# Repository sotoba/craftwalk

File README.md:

# craftWalk

macro pad for (mine)?(crafter|creator).

## Documents

- [build guide](docs/build_guid.md)
- [default keymap](docs/keymap.md)

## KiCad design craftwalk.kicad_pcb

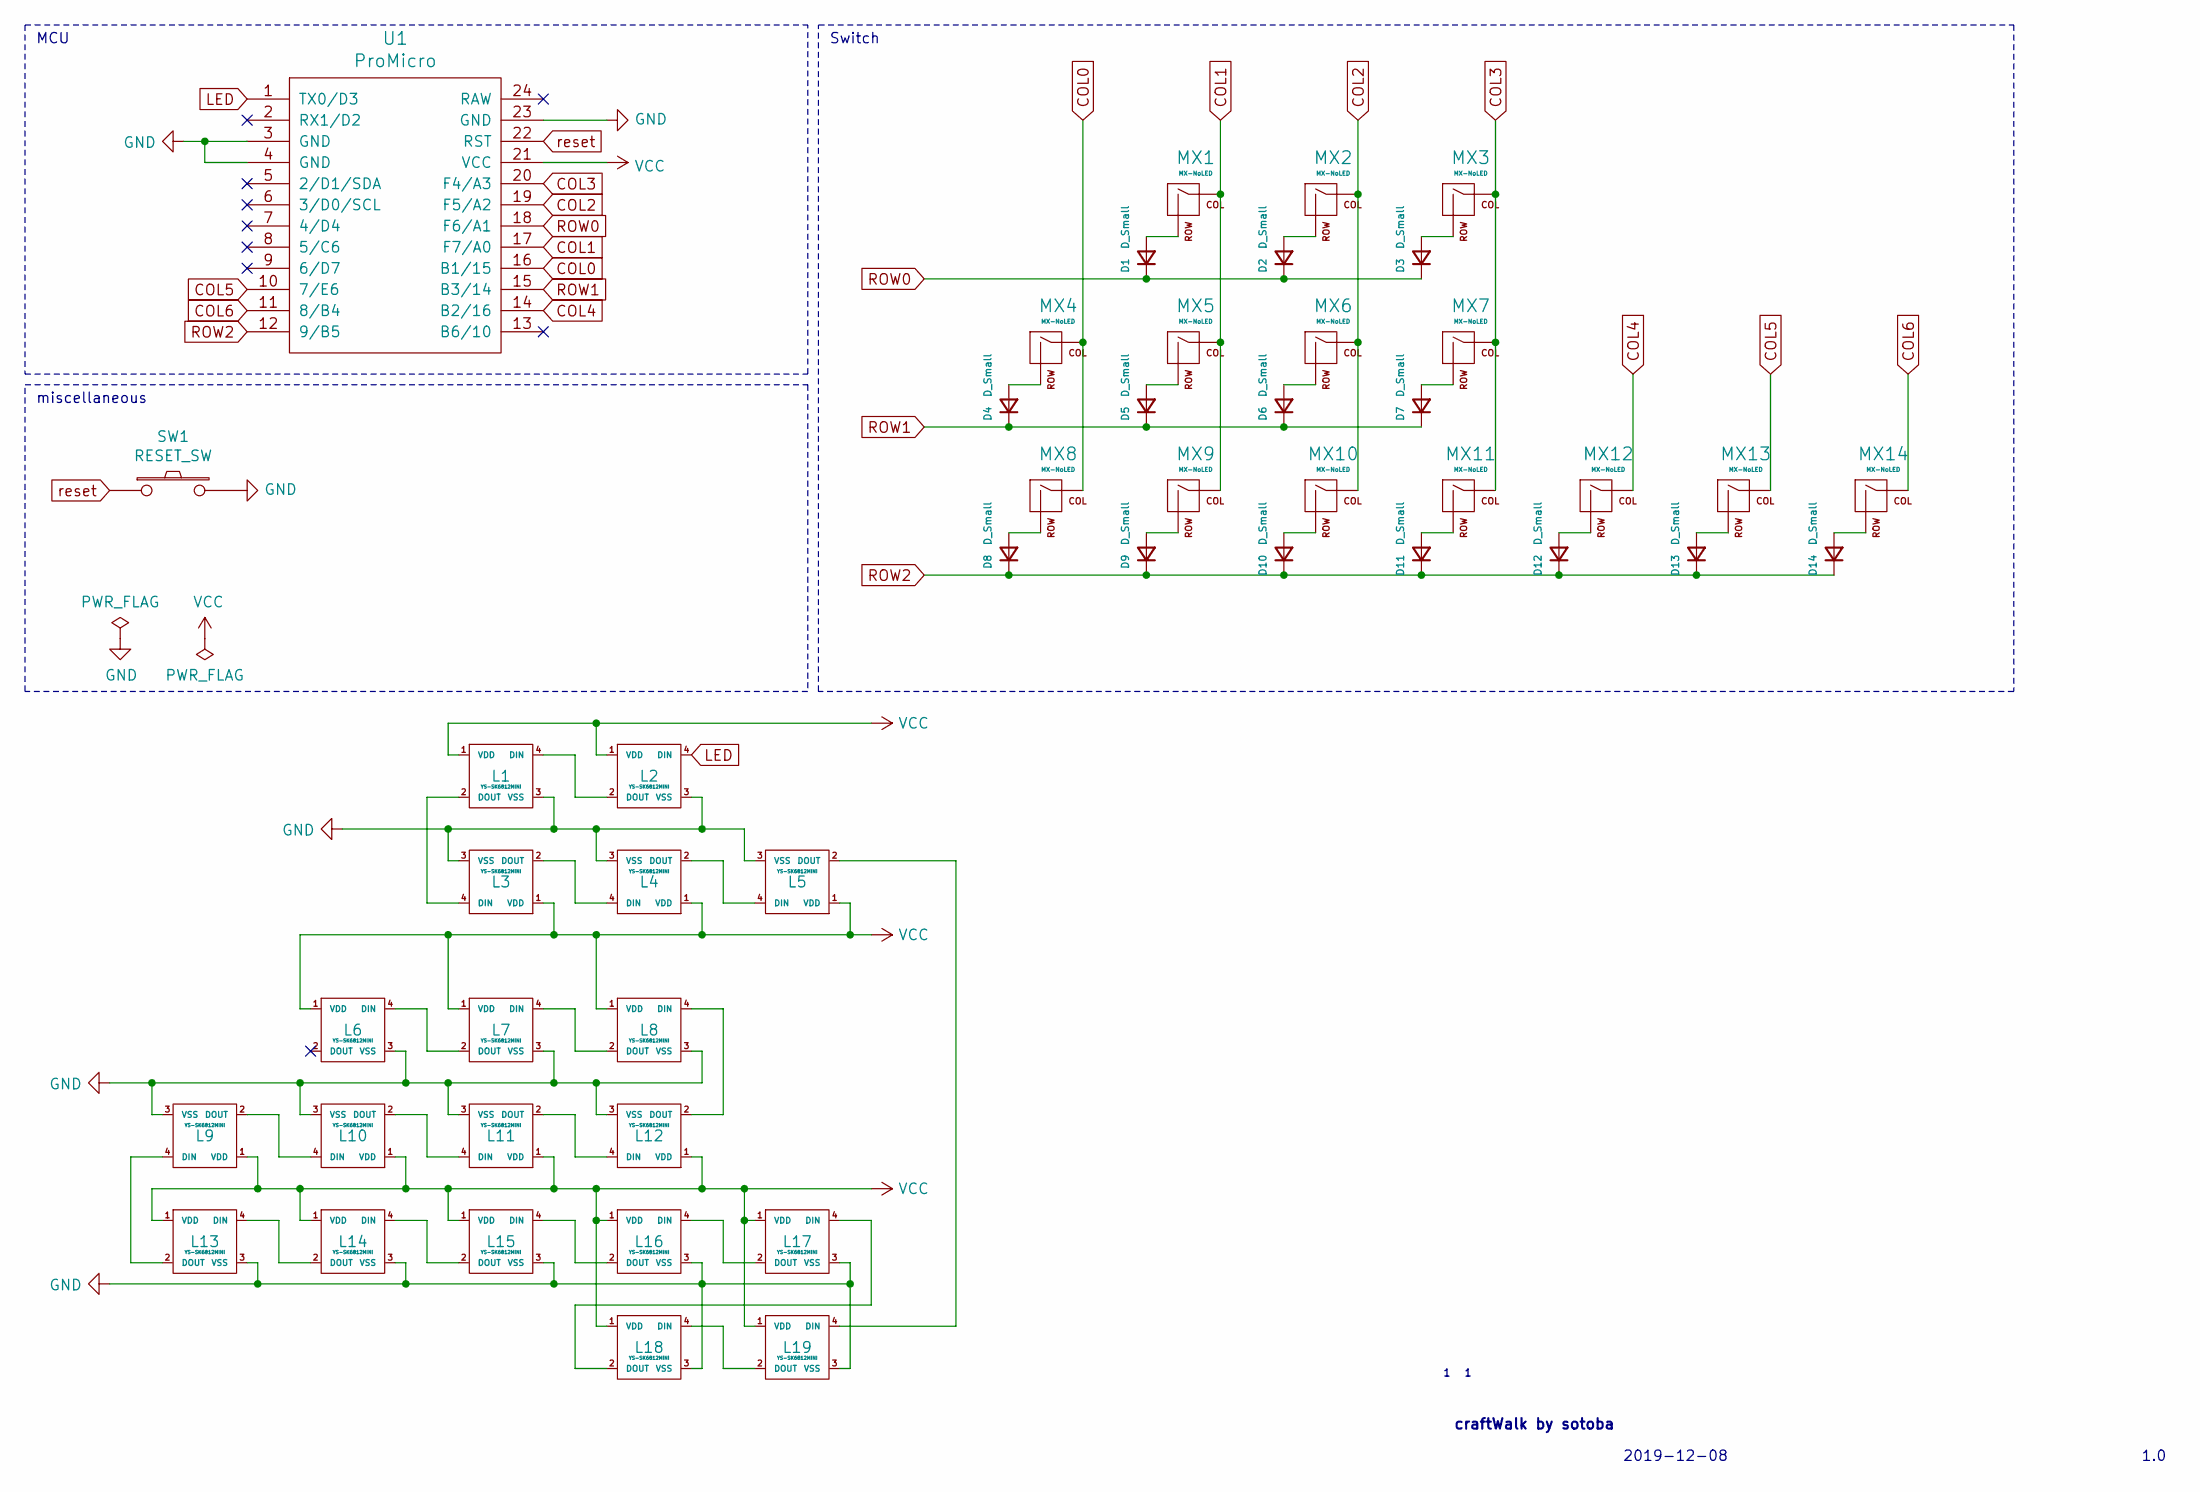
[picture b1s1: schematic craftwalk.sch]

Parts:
D1, D2, D3, D4, D5, D6, D7, D8, D9, D10, D11, D12, D13, D14: D_Small; D3_SMD
L1, L2, L3, L4, L5: YS-SK6812MINI; YS-SK6812
L6, L7, L8, L9, L10, L11, L12, L13, L14, L15, L16, L17, L18, L19: YS-SK6812MINI; YS-SK6812-underglow
MX1, MX2, MX3, MX4, MX5, MX6, MX7, MX8, MX9, MX10, MX11, MX12: MX-NoLED; MXOnly-1U-Hotswap
MX13, MX14: MX-NoLED; MXOnly-1.5U-Hotswap
SW1: RESET_SW; SKQGADE010
U1: ProMicro; ProMicro_v2

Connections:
COL0: MX4.1 (COL), MX8.1 (COL), U1.16 (B1/15)
COL1: MX1.1 (COL), MX5.1 (COL), MX9.1 (COL), U1.17 (F7/A0)
COL2: MX2.1 (COL), MX6.1 (COL), MX10.1 (COL), U1.19 (F5/A2)
COL3: MX3.1 (COL), MX7.1 (COL), MX11.1 (COL), U1.20 (F4/A3)
COL4: MX12.1 (COL), U1.14 (B2/16)
COL5: MX13.1 (COL), U1.10 (7/E6)
COL6: MX14.1 (COL), U1.11 (8/B4)
GND: L1.3 (VSS), L2.3 (VSS), L3.3 (VSS), L4.3 (VSS), L5.3 (VSS), L6.3 (VSS), L7.3 (VSS), L8.3 (VSS), L9.3 (VSS), L10.3 (VSS), L11.3 (VSS), L12.3 (VSS), L13.3 (VSS), L14.3 (VSS), L15.3 (VSS), L16.3 (VSS), L17.3 (VSS), L18.3 (VSS), L19.3 (VSS), SW1.2, U1.3 (GND), U1.4 (GND), U1.23 (GND)
LED: L2.4 (DIN), U1.1 (TX0/D3)
unnamed: D1.2 (A), MX1.2 (ROW)
unnamed: D2.2 (A), MX2.2 (ROW)
unnamed: D3.2 (A), MX3.2 (ROW)
unnamed: D4.2 (A), MX4.2 (ROW)
unnamed: D5.2 (A), MX5.2 (ROW)
unnamed: D6.2 (A), MX6.2 (ROW)
unnamed: D7.2 (A), MX7.2 (ROW)
unnamed: D8.2 (A), MX8.2 (ROW)
unnamed: D9.2 (A), MX9.2 (ROW)
unnamed: D10.2 (A), MX10.2 (ROW)
unnamed: D11.2 (A), MX11.2 (ROW)
unnamed: D12.2 (A), MX12.2 (ROW)
unnamed: D13.2 (A), MX13.2 (ROW)
unnamed: D14.2 (A), MX14.2 (ROW)
unnamed: L1.2 (DOUT), L3.4 (DIN)
unnamed: L1.4 (DIN), L2.2 (DOUT)
unnamed: L3.2 (DOUT), L4.4 (DIN)
unnamed: L4.2 (DOUT), L5.4 (DIN)
unnamed: L6.4 (DIN), L7.2 (DOUT)
unnamed: L7.4 (DIN), L8.2 (DOUT)
unnamed: L10.2 (DOUT), L11.4 (DIN)
unnamed: L9.2 (DOUT), L10.4 (DIN)
unnamed: L11.2 (DOUT), L12.4 (DIN)
unnamed: L8.4 (DIN), L12.2 (DOUT)
unnamed: L9.4 (DIN), L13.2 (DOUT)
unnamed: L13.4 (DIN), L14.2 (DOUT)
unnamed: L14.4 (DIN), L15.2 (DOUT)
unnamed: L15.4 (DIN), L16.2 (DOUT)
unnamed: L16.4 (DIN), L17.2 (DOUT)
unnamed: L17.4 (DIN), L18.2 (DOUT)
unnamed: L18.4 (DIN), L19.2 (DOUT)
unnamed: L5.2 (DOUT), L19.4 (DIN)
ROW0: D1.1 (K), D2.1 (K), D3.1 (K), U1.18 (F6/A1)
ROW1: D4.1 (K), D5.1 (K), D6.1 (K), D7.1 (K), U1.15 (B3/14)
ROW2: D8.1 (K), D9.1 (K), D10.1 (K), D11.1 (K), D12.1 (K), D13.1 (K), D14.1 (K), U1.12 (9/B5)
VCC: L1.1 (VDD), L2.1 (VDD), L3.1 (VDD), L4.1 (VDD), L5.1 (VDD), L6.1 (VDD), L7.1 (VDD), L8.1 (VDD), L9.1 (VDD), L10.1 (VDD), L11.1 (VDD), L12.1 (VDD), L13.1 (VDD), L14.1 (VDD), L15.1 (VDD), L16.1 (VDD), L17.1 (VDD), L18.1 (VDD), L19.1 (VDD), U1.21 (VCC)
reset: SW1.1, U1.22 (RST)

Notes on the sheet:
craftWalk by sotoba
2019-12-08
1.0
MCU
Switch
miscellaneous

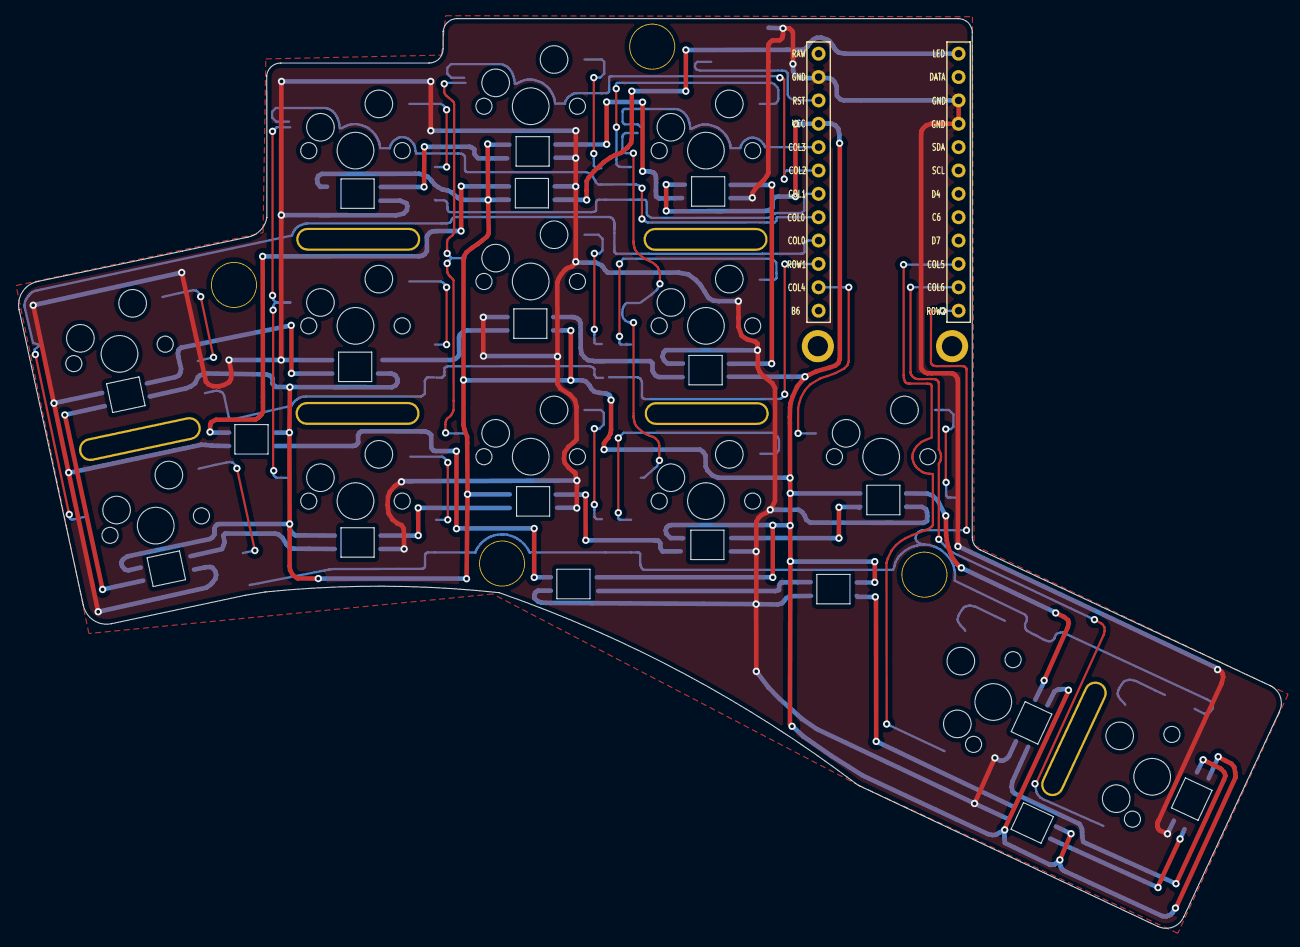
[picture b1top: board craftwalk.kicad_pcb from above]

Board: 2 copper layers, 137.3 x 98.9 mm, 53 parts (1 on the bottom side), 46 nets.

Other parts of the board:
Ref**: Val**; HOLE
Ref**#2, Ref**#3, Ref**#4: Val**; HOLE

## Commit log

2019-11-21 Initalize Project
2019-11-30 set schema
2019-12-28 precreate
2020-07-09 add main view image
2020-07-26 rev 1.2
    - add LED support
    - change libs to submodule
    - refactor
2020-08-02 add build guide images
2020-08-03 add image to readme
2020-08-03 resize images
2020-08-03 add keymap images
2020-08-03 add keymap page
2020-08-03 fix layer image
2020-08-05 Create LICENSE
2020-10-08 fix symbol link
2020-10-08 fix default keymap image
2021-06-13 add firmware manual on GUI
